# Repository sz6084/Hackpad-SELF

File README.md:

# Sammie's Scarapad
A macropad with some Scaramouche art on it!

### Inspiration

I wanted to create a macropad for the keys I lost when i moved from daily-driving a laptop to a PC. Specifically, keys like Rewind, Play/Pause, and Next. These keys were not part of my laptop's function key alternates-they were dedicated buttons which I missed since my current keyboard, a (surprisingly decent and fully-sized) membrane keyboard, only had function keys with no dedicated media buttons. This is definitely not something everyone agrees with (and I find binding my function keys would be too tedious, especially since my old laptop did not have these bound to function keys anyways). It has 16 switches (numpad functions too!), 1 rp2040, and no LEDs (I don't want the hassle and my membrane keyboard doesn't have it anyways, thought RGB in a future macropad would be cool). Something else I might consider is using Choc v2 switches but since the guide used Cherry MX switches I decided to do the same. Also Genshin Impact.

### Challenge

I had never designed a macropad before, let alone use Fusion360 or KiCAD at all. I followed the online guide (thanks @Cyao but please update it!) and consulted my trusty friend who had more experience than I did. I also asked questions in the Hack Club Slack.

### Specifications

BOM:
 - 16x Cherry MX switches
 - 16x 1N4148 diodes
 - 1x XIAO RP2040
 - 16x Blank DSA keycaps
 - 4x M3x16 Bolt
 - 4x M3 Heatset

Others:
 - KMK firmware
 - TopCase.stl (as soon as I sort my files!)
 - Bottomcase.stl (as soon as I sort my files!)

Schematic            |  PCB         |   Case
:-------------------------:|:-------------------------:|:-------------------------:|
  |    |

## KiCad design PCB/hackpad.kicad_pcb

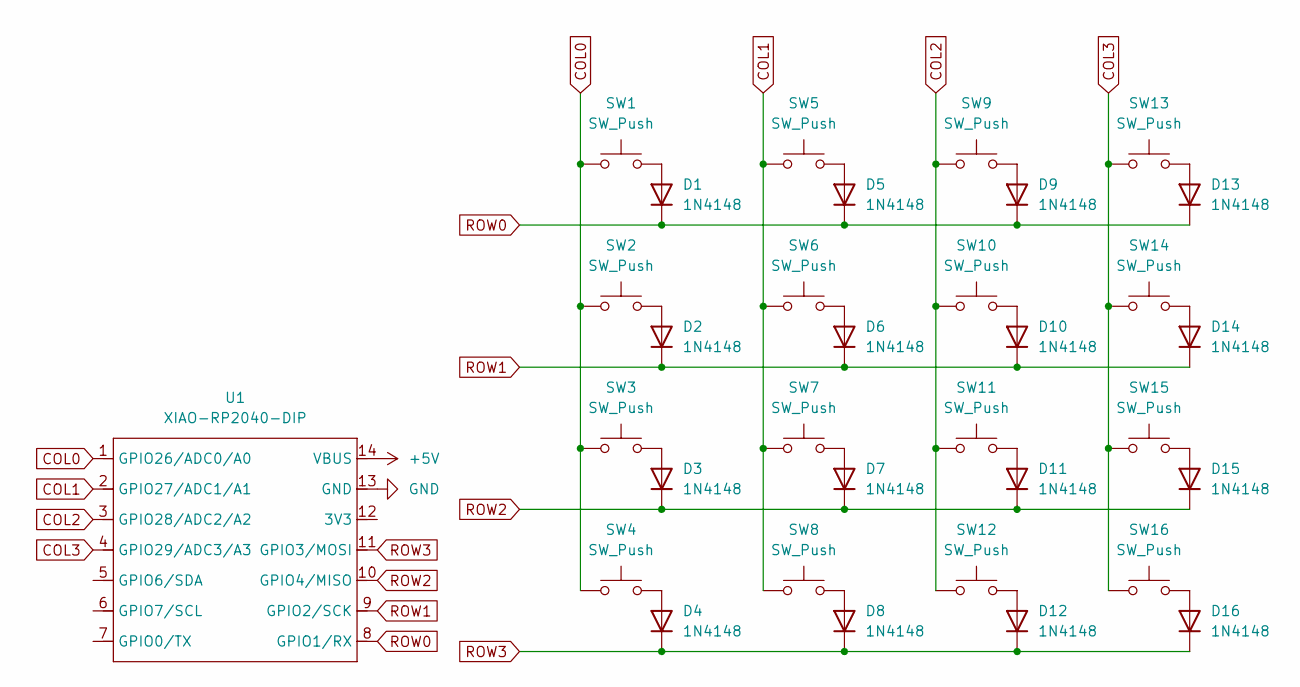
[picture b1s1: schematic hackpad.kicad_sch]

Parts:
D1, D2, D3, D4, D5, D6, D7, D8, D9, D10, D11, D12, D13, D14, D15, D16: 1N4148; D_DO-35_SOD27_P7.62mm_Horizontal
SW1, SW2, SW3, SW4, SW5, SW6, SW7, SW9, SW10, SW11, SW12, SW13, SW14, SW15, SW16: SW_Push; SW_Cherry_MX_1.00u_PCB
SW8: SW_Push; SW_Cherry_MX_2.00u_PCB
U1: XIAO-RP2040-DIP

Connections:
+5V: U1.14 (VBUS)
COL0: SW1.1, SW2.1, SW3.1, SW4.1, U1.1 (GPIO26/ADC0/A0)
COL1: SW5.1, SW6.1, SW7.1, SW8.1, U1.2 (GPIO27/ADC1/A1)
COL2: SW9.1, SW10.1, SW11.1, SW12.1, U1.3 (GPIO28/ADC2/A2)
COL3: SW13.1, SW14.1, SW15.1, SW16.1, U1.4 (GPIO29/ADC3/A3)
GND: U1.13 (GND)
unnamed: D1.2 (A), SW1.2
unnamed: D2.2 (A), SW2.2
unnamed: D3.2 (A), SW3.2
unnamed: D4.2 (A), SW4.2
unnamed: D5.2 (A), SW5.2
unnamed: D6.2 (A), SW6.2
unnamed: D7.2 (A), SW7.2
unnamed: D8.2 (A), SW8.2
unnamed: D9.2 (A), SW9.2
unnamed: D10.2 (A), SW10.2
unnamed: D11.2 (A), SW11.2
unnamed: D12.2 (A), SW12.2
unnamed: D13.2 (A), SW13.2
unnamed: D14.2 (A), SW14.2
unnamed: D15.2 (A), SW15.2
unnamed: D16.2 (A), SW16.2
ROW0: D1.1 (K), D5.1 (K), D9.1 (K), D13.1 (K), U1.8 (GPIO1/RX)
ROW1: D2.1 (K), D6.1 (K), D10.1 (K), D14.1 (K), U1.9 (GPIO2/SCK)
ROW2: D3.1 (K), D7.1 (K), D11.1 (K), D15.1 (K), U1.10 (GPIO4/MISO)
ROW3: D4.1 (K), D8.1 (K), D12.1 (K), D16.1 (K), U1.11 (GPIO3/MOSI)

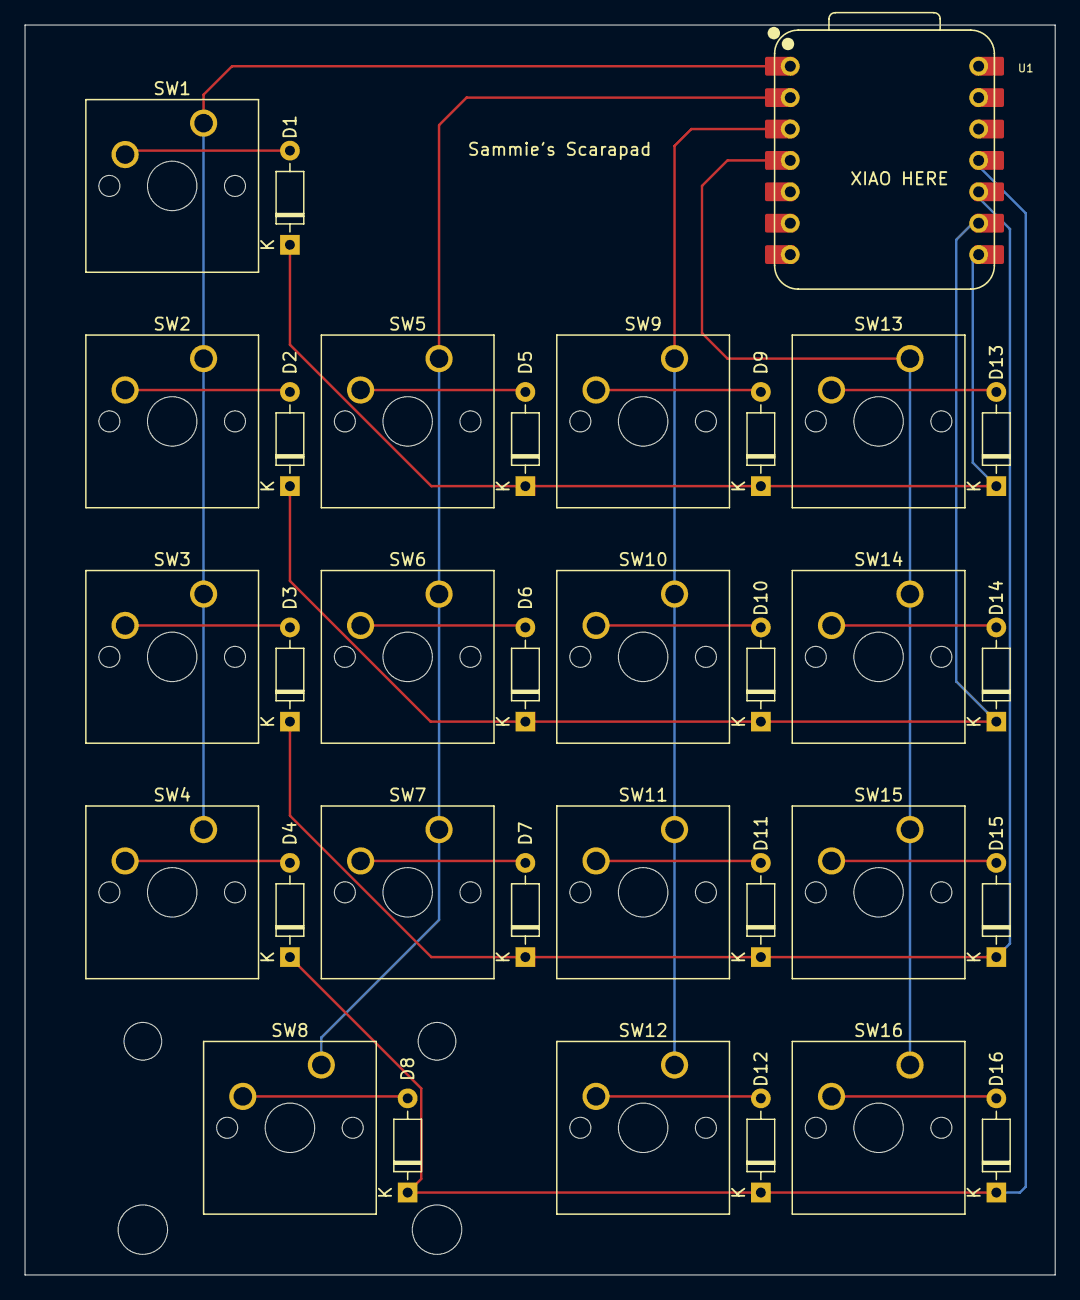
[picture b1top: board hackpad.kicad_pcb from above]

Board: 2 copper layers, 83.3 x 101.1 mm, 33 parts (0 on the bottom side), 24 nets.

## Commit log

2025-02-16 updated paths of symbol and footprint libraries
2025-02-16 Added branding to PCB and adjusted MC to spec
2025-02-17 Finished Top plate and changed case. Added 3d model of PCB and other relevant components.
2025-02-17 Updated PCB and step file
2025-02-17 added starter code for firmware (kmk)
2025-02-19 Updated firmware pins
2025-02-19 Updated keymap in kmk firmware
2025-02-21 Updated switch 8 to 2u size
2025-02-21 Added silkscreen art
2025-02-21 renamed: hackpad.step -> hackpad_pcb.step
2025-02-21 Updated file structure
2025-02-21 Uploaded CAD file
2025-02-21 Added prod
2025-02-21 modified: hackpad.kicad_pro
2025-02-21 modified: PCB/hackpad.kicad_pro modified: hackpad_pcb.step
2025-02-21 Updated name
2025-02-23 Added 3d Models
